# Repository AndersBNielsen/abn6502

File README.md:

# ABNielsen.com 6502 Single Board Computer Revision 2

## Browser emulator

The self-contained [browser emulator](emulator/README.md) runs the real ABN6502 r2 ROM. [Try it online](https://www.imania.dk/abn6502-emulator/). From `emulator/`, run `npm test` and `npm run build`. Emulator code and bundled hardware/firmware assets have separate licenses; see [emulator/LICENSE.md](emulator/LICENSE.md).

This is a 6502-based complete single board computer intended to help during the global IC shortage. Why use new chips when you can reuse scrap?

## Update Update! The newest ABN6502 SBC R2 board is available as:
- Blank PCBs 
- Fully mounted PCBs including sockets and headers
- Kits with SMD components presoldered, limiting soldering to though hole components/sockets. 

All gold plated (ENIG) PCBs: https://www.imania.dk/index.php?currency=EUR&cPath=204&sort=5a&language=en

Coming soon: R2 video. 

Complete hardware overview of R1:

Video about the wireless bootloader:

Check out the NEW project on HackADay if you want to read more and see some pretty pictures :)

https://hackaday.io/project/184725-abn6502-sbc-r1

For R1 I got rid of the Padauk MCU without increasing the chip count!

# Build instructions:

1) Send gerber files from /hardware to your favorite board house (see "Getting a PCB" below) (or get a board from [my store](https://www.imania.dk/index.php?currency=EUR&cPath=204&sort=5a&language=en)) 
2) Build the firmware using assemble.sh (macOS/Linux) - this will also try to burn the main ROM using Minipro. Dependencies: [CC65] (https://github.com/cc65/cc65) and a way to burn the ROM's.
3) Source the IC's - the spirit of this project is to contribute as little as possible to the global IC shortage and get used chips locally or from Ebay/AliExpress/etc.
4) Burn the ROMs. I use a TL866II Plus variant for the actual ROMs.
5) Solder away. If you can solder 0805 components(poorly), you should be fine. Some optional components (the microUSB connector, the 3v3 regulator, and the RF-module) require a bit more skill.  
6) For the PS/2-keyboard I use the 6522's Shift Register, PB6, and a 74xx74 flip flop.  See my R1 Hardware overview at 7:46: https://youtu.be/w5cA64xof2I?t=466 This is now included on the board - instead of a PS/2 connector which can be harder to source I went with a USB-A-connector. Keyboard plugs straight into the board. 
7) Enjoy!

Optional:
Setup SSH keys with a Raspberry Pi, connect an nRF24L01+ compatible module to it and compile the wireless bootloader code in /software_linux

Also optional:
Microsoft BASIC can be enabled by cloning the msbasic Github repo into the same folder you cloned this repo.

> git clone https://github.com/mist64/msbasic.git

Then uncomment ;BASIC := 1 (Remove the ";") and run assemble.sh - this will let you run BASIC by pressing F4.
To change settings for BASIC, values can be changed in defines_abn6502.s

Also, please note that the current code assumes VRAM starts at $0800 rather than the default $2000 in the schematic - resistors will have pads for configuring in the next build, but for now it requires jumpers.

License: Attribution-NonCommercial 4.0 International (CC BY-NC 4.0) https://creativecommons.org/licenses/by-nc/4.0/

## Getting a PCB
This project is kindly sponsored by JLCPCB. They offer cheap, professional looking PCBs and super fast delivery.

Step 1: Get the gerber file zip package from the /hardware/jlc folder
[hardware/jlcpcb/production_files/GERBER-6502.zip](hardware/jlcpcb/production_files/GERBER-6502.zip) for instance.

Step 2: Upload to JLCPCB [https://jlcpcb.com/?from=Anders_N](https://jlcpcb.com/?from=Anders_N)

Step 3: Pick your color, surface finish and order.

You can use these affiliate links to get a board for $2 and also get $54 worth of New User Coupons at: https://jlcpcb.com/?from=Anders_N

And in case you also want to order a 3D-printed case you can use this link. 
How to Get a $7 3D Printing Coupon: [https://3d.jlcpcb.com/?from=Anders3DP](https://jlc3dp.com/?from=Anders_N)

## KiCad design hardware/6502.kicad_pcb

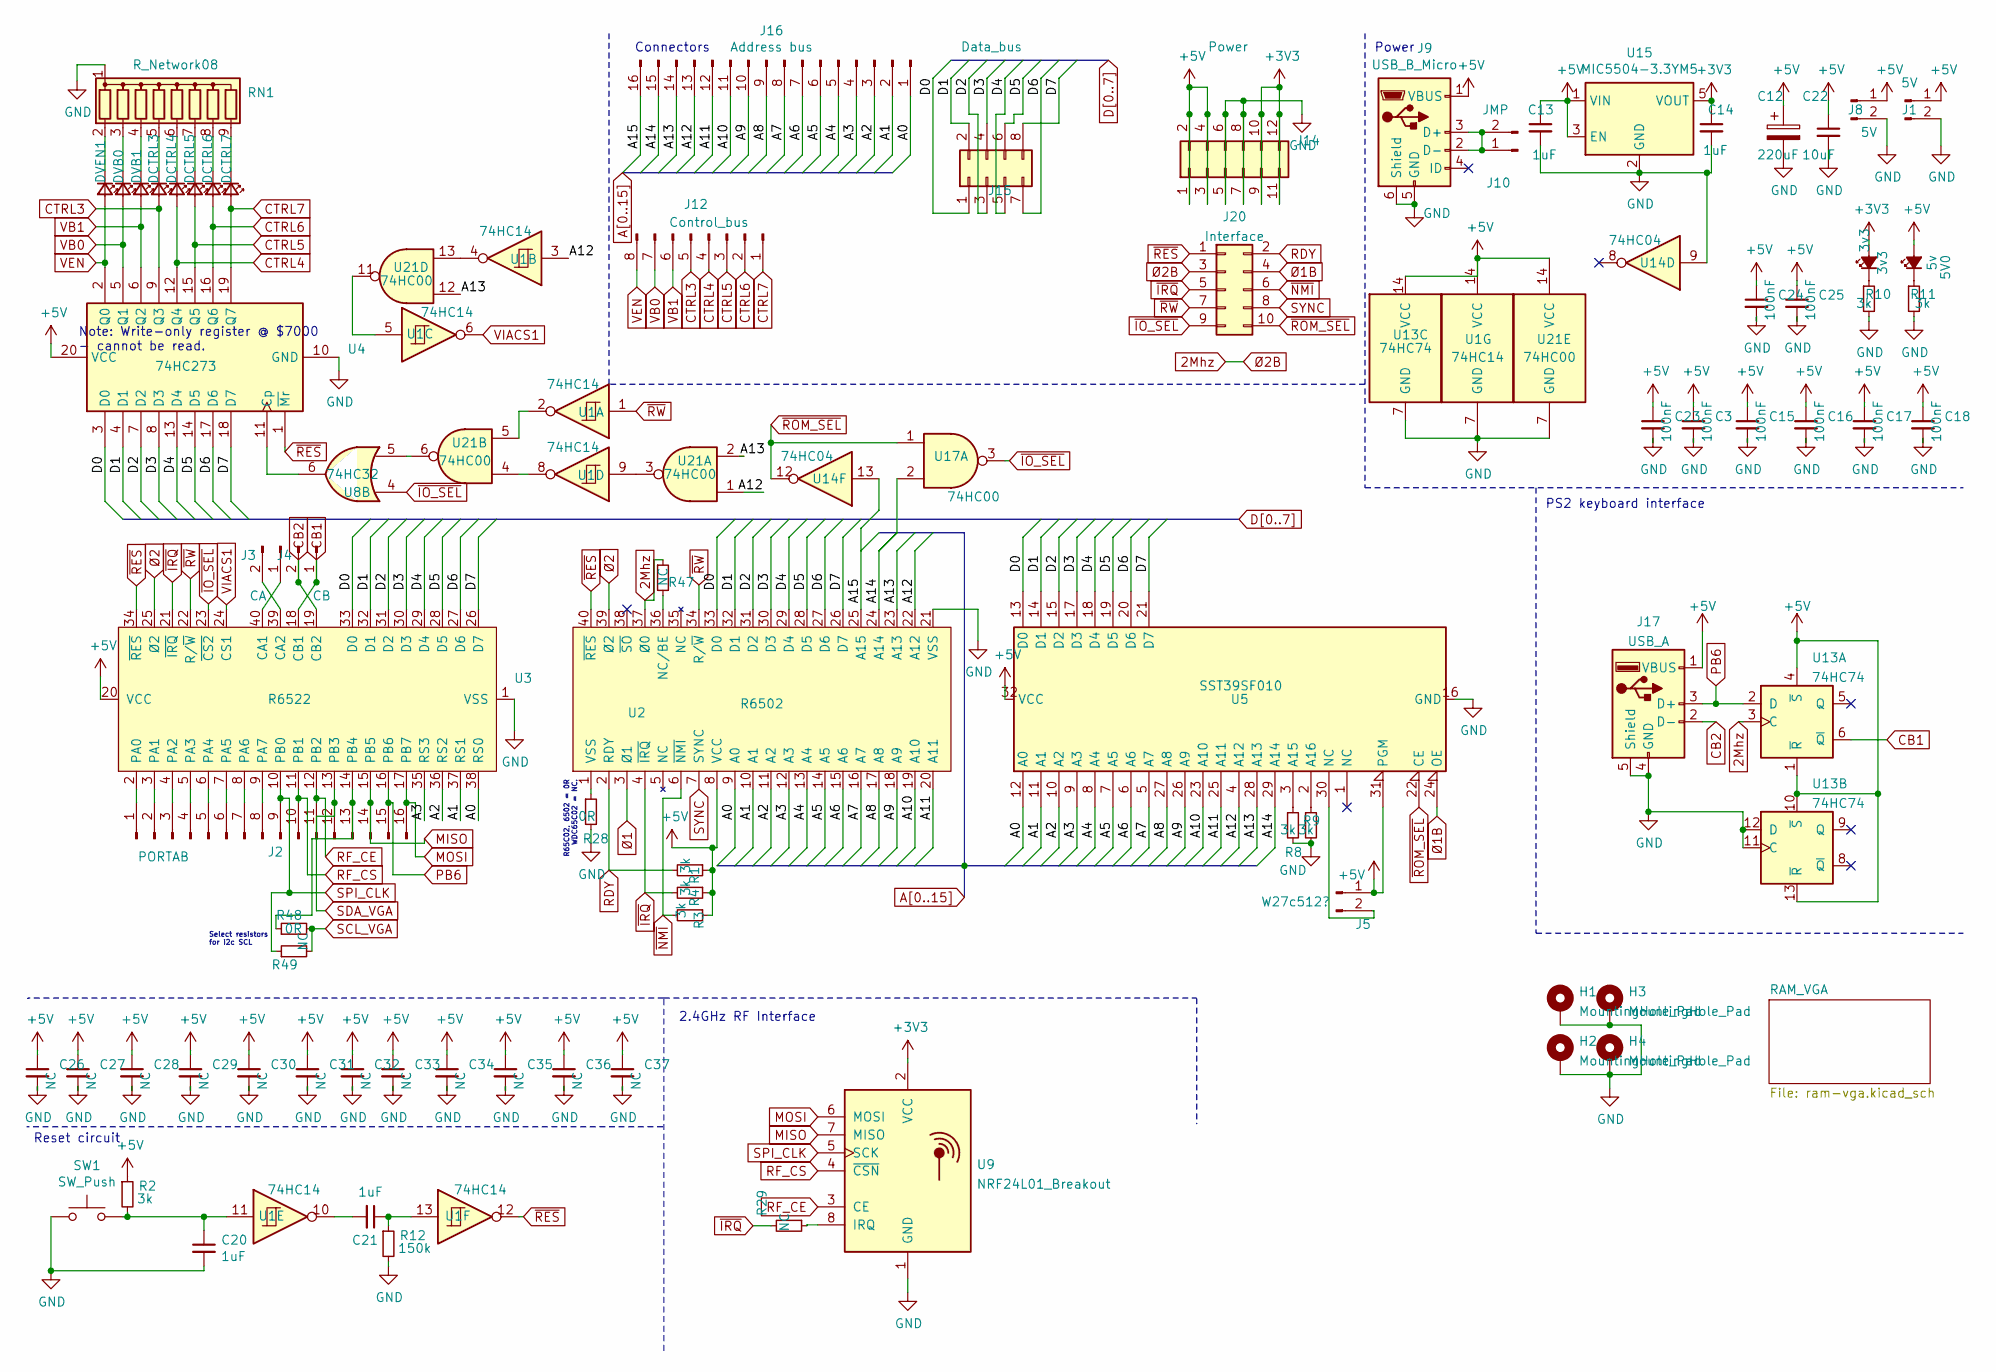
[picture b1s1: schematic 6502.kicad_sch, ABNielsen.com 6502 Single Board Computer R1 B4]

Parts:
3v3: 3v3; LED_0805_2012Metric; LCSC C84256
5V0: 5v; LED_0805_2012Metric; LCSC C84256
C3, C15, C16, C17, C18, C23, C24, C25: 100nF; C_0603_1608Metric
C12: 220uF; CP_Elec_6.3x7.7; LCSC C131120
C13, C14, C20, C21: 1uF; C_0805_2012Metric
C22: 10uF; C_0805_2012Metric
C26, C27, C28, C29, C30, C31, C32, C33, C34, C35, C36, C37: NC; C_0805_2012Metric
DCTRL3, DCTRL4, DCTRL5, DCTRL6, DCTRL7: RED; LED_0805_2012Metric; LCSC C84256
DVB0, DVB1: RED; LED_0805_2012Metric; LCSC C84256
DVEN1: RED; LED_0805_2012Metric; LCSC C84256
H1, H2, H3, H4: MountingHole_Pad; MountingHole_4.3mm_M4_ISO14580_Pad
J1, J8: 5V; PinHeader_1x02_P2.54mm_Vertical
J2: PORTAB; PinHeader_1x16_P2.54mm_Vertical
J3: CA; PinHeader_1x02_P2.54mm_Vertical
J4: CB; PinHeader_1x02_P2.54mm_Vertical
J5: W27c512?; PinHeader_1x02_P2.54mm_Vertical
J9: USB_B_Micro; USB_Micro-B_Amphenol_10118194_Horizontal; LCSC C132563
J10: JMP; PinHeader_1x02_P2.54mm_Vertical
J12: Control_bus; PinHeader_1x08_P2.54mm_Vertical
J14: Power; PinHeader_2x06_P2.54mm_Vertical
J15: Data_bus; PinHeader_2x04_P2.54mm_Vertical
J16: Address bus; PinHeader_2x08_P2.54mm_Vertical
J17: USB_A; USB_A_Molex_67643_Horizontal
J20: Interface; PinHeader_2x05_P2.54mm_Vertical
R1, R2, R3, R4, R8, R9, R10, R11: 3k; R_0805_2012Metric
R12: 150k; R_0805_2012Metric
R28: 0R; SolderJumper-2_P1.3mm_Open_RoundedPad1.0x1.5mm
R29, R47: NC; SolderJumper-2_P1.3mm_Open_RoundedPad1.0x1.5mm
R48: 0R; R_0805_2012Metric
R49: NC; R_0805_2012Metric
RN1: R_Network08; R_Array_SIP9
SW1: SW_Push; SW_SPST_TL3342; LCSC C318884
U1: 74HC14; DIP-14_W7.62mm
U2: R6502; DIP-40_W15.24mm
U3: R6522; DIP-40_W15.24mm
U4: 74HC273; DIP-20_W7.62mm
U5: SST39SF010; DIP_Socket-32_W11.9_W12.7_W15.24_W17.78_W18.5_3M_232-1285-0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
U8: 74HC32; DIP-14_W7.62mm
U9: NRF24L01_Breakout; NRF24L01-SMD
U13: 74HC74; DIP-14_W7.62mm
U14: 74HC04; DIP-14_W7.62mm
U15: MIC5504-3.3YM5; SOT-23-5; LCSC C3021093
U17, U21: 74HC00; DIP-14_W7.62mm

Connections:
2Mhz: J20.3, R47.1, U2.37 (Ø0), U13.3 (C); also elsewhere on the board
+3V3: 3v3.2 (A), C14.1, J14.9, J14.10, J14.11, J14.12, U9.2 (VCC), U15.5 (VOUT)
+5V: 5V0.2 (A), C3.1, C12.1, C13.1, C15.1, C16.1, C17.1, C18.1, C22.1, C23.1, C24.1, C25.1, C26.1, C27.1, C28.1, C29.1, C30.1, C31.1, C32.1, C33.1, C34.1, C35.1, C36.1, C37.1, J1.1, J5.1, J8.1, J9.1 (VBUS), J9.A4 (VBUS), J9.A9 (VBUS), J9.B4 (VBUS), J9.B9 (VBUS), J14.1, J14.2, J14.3, J14.4, J17.1 (VBUS), R1.1, R2.1, R3.1, R4.1, U1.14 (VCC), U2.8 (VCC), U3.20 (VCC), U4.20 (VCC), U5.31 (PGM), U5.32 (VCC), U13.1 (~R), U13.4 (~S), U13.10 (~S), U13.13 (~R), U13.14 (VCC), U15.1 (VIN), U15.3 (EN), U21.14 (VCC); also elsewhere on the board
A0: J16.1, U2.9 (A0), U3.38 (RS0), U5.12 (A0); also elsewhere on the board
A1: J16.2, U2.10 (A1), U3.37 (RS1), U5.11 (A1); also elsewhere on the board
A2: J16.3, U2.11 (A2), U3.36 (RS2), U5.10 (A2); also elsewhere on the board
A3: J16.4, U2.12 (A3), U3.35 (RS3), U5.9 (A3); also elsewhere on the board
A4: J16.5, U2.13 (A4), U5.8 (A4); also elsewhere on the board
A5: J16.6, U2.14 (A5), U5.7 (A5); also elsewhere on the board
A6: J16.7, U2.15 (A6), U5.6 (A6); also elsewhere on the board
A7: J16.8, U2.16 (A7), U5.5 (A7); also elsewhere on the board
A8: J16.9, U2.17 (A8), U5.27 (A8); also elsewhere on the board
A9: J16.10, U2.18 (A9), U5.26 (A9); also elsewhere on the board
A10: J16.11, U2.19 (A10), U5.23 (A10); also elsewhere on the board
A11: J16.12, U2.20 (A11), U5.25 (A11); also elsewhere on the board
A12: J16.13, U1.3, U2.22 (A12), U5.4 (A12), U21.1; also elsewhere on the board
A13: J16.14, U2.23 (A13), U5.28 (A13), U21.2, U21.12; also elsewhere on the board
A14: J16.15, U2.24 (A14), U5.29 (A14), U17.2; also elsewhere on the board
A15: J16.16, U2.25 (A15), U14.13; also elsewhere on the board
CB1: J4.1, U3.18 (CB1), U13.6 (~Q)
CB2: J4.2, J17.2 (D-), U3.19 (CB2)
CTRL3: DCTRL3.2 (A), J12.5, U4.9 (Q3); also elsewhere on the board
CTRL4: DCTRL4.2 (A), J12.4, U4.12 (Q4); also elsewhere on the board
CTRL5: DCTRL5.2 (A), J12.3, U4.15 (Q5); also elsewhere on the board
CTRL6: DCTRL6.2 (A), J12.2, U4.16 (Q6); also elsewhere on the board
CTRL7: DCTRL7.2 (A), J12.1, U4.19 (Q7)
D0: J15.1, U2.33 (D0), U3.33 (D0), U4.3 (D0), U5.13 (D0); also elsewhere on the board
D1: J15.2, U2.32 (D1), U3.32 (D1), U4.4 (D1), U5.14 (D1); also elsewhere on the board
D2: J15.3, U2.31 (D2), U3.31 (D2), U4.7 (D2), U5.15 (D2); also elsewhere on the board
D3: J15.4, U2.30 (D3), U3.30 (D3), U4.8 (D3), U5.17 (D3); also elsewhere on the board
D4: J15.5, U2.29 (D4), U3.29 (D4), U4.13 (D4), U5.18 (D4); also elsewhere on the board
D5: J15.6, U2.28 (D5), U3.28 (D5), U4.14 (D5), U5.19 (D5); also elsewhere on the board
D6: J15.7, U2.27 (D6), U3.27 (D6), U4.17 (D6), U5.20 (D6); also elsewhere on the board
D7: J15.8, U2.26 (D7), U3.26 (D7), U4.18 (D7), U5.21 (D7); also elsewhere on the board
MISO: J2.14, U3.15 (PB5), U9.7 (MISO)
MOSI: J2.16, U3.17 (PB7), U9.6 (MOSI)
unnamed: 3v3.1 (K), R10.1
unnamed: 5V0.1 (K), R11.1
unnamed: C20.1, R2.2, SW1.2, U1.11
unnamed: C21.1, R12.1, U1.13
unnamed: C21.2, U1.10
unnamed 65: DCTRL3.1 (K), RN1.5 (R4); also elsewhere on the board
unnamed 66: DCTRL4.1 (K), RN1.6 (R5); also elsewhere on the board
unnamed 67: DCTRL5.1 (K), RN1.7 (R6); also elsewhere on the board
unnamed 68: DCTRL6.1 (K), RN1.8 (R7); also elsewhere on the board
unnamed 69: DCTRL7.1 (K), RN1.9 (R8); also elsewhere on the board
unnamed 70: DVB0.1 (K), RN1.3 (R2); also elsewhere on the board
unnamed 71: DVB1.1 (K), RN1.4 (R3); also elsewhere on the board
unnamed 72: DVEN1.1 (K), RN1.2 (R1); also elsewhere on the board
unnamed: J2.1, U3.2 (PA0)
unnamed: J2.2, U3.3 (PA1)
unnamed: J2.3, U3.4 (PA2)
unnamed: J2.4, U3.5 (PA3)
unnamed: J2.5, U3.6 (PA4)
unnamed: J2.6, U3.7 (PA5)
unnamed: J2.7, U3.8 (PA6)
unnamed: J2.8, U3.9 (PA7)
unnamed: J3.1, U3.40 (CA1)
unnamed: J3.2, U3.39 (CA2)
unnamed: J5.2, U5.30 (NC)
unnamed 85: J9.A5 (CC1); also elsewhere on the board
unnamed 86: J9.B5 (CC2); also elsewhere on the board
unnamed: U1.2, U21.5
unnamed: U1.4, U21.13
unnamed: U1.5, U21.11
unnamed: U1.8, U21.4
unnamed: U1.9, U21.3
unnamed: R47.2, U2.36 (NC/BE)
unnamed: U4.11 (Cp), U8.6
unnamed: R8.1, U5.3 (A15)
unnamed: R9.1, U5.2 (A16)
unnamed: R29.1, U9.8 (IRQ)
unnamed: U8.5, U21.6
PB6: J2.15, J17.3 (D+), U3.16 (PB6), U13.2 (D)
RDY: J20.2, R1.2, U2.2 (RDY)
RF_CE: J2.11, U3.12 (PB2), U9.3 (CE)
RF_CS: J2.10, U3.11 (PB1), U9.4 (~CSN)
SDA_VGA: J2.12, U3.13 (PB3); also elsewhere on the board
SPI_CLK: J2.9, R49.1, U3.10 (PB0), U9.5 (SCK)
SYNC: J20.8, U2.7 (SYNC)
VB0: DVB0.2 (A), J12.7, U4.5 (Q1); also elsewhere on the board
VB1: DVB1.2 (A), J12.6, U4.6 (Q2); also elsewhere on the board
VEN: DVEN1.2 (A), J12.8, U4.2 (Q0); also elsewhere on the board
VIACS1: U1.6, U3.24 (CS1)
~IO_SEL: J20.9, U3.23 (~CS2), U8.4, U17.3
~IRQ: J20.5, R4.2, R29.2, U2.4 (~IRQ), U3.21 (~IRQ)
~NMI: J20.6, R3.2, U2.6 (~NMI)
~RES: J20.1, U1.12, U2.40 (~RES), U3.34 (~RES), U4.1 (~Mr)
~ROM_SEL: J20.10, U5.22 (CE), U14.12, U17.1
~RW: J20.7, U1.1, U2.34 (R/~W), U3.22 (R/~W); also elsewhere on the board
Ø1: U2.3 (Ø1)
Ø1B: J20.4, U5.24 (OE); also elsewhere on the board
Ø2: U2.39 (Ø2), U3.25 (Ø2)

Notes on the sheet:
Note: Write-only register @ $7000 - cannot be read.
Select resistors for i2c SCL
Power
R65C02, 6502 = 0R WDC65C02 = NC.
Reset circuit
Connectors
PS2 keyboard interface
2.4GHz RF Interface

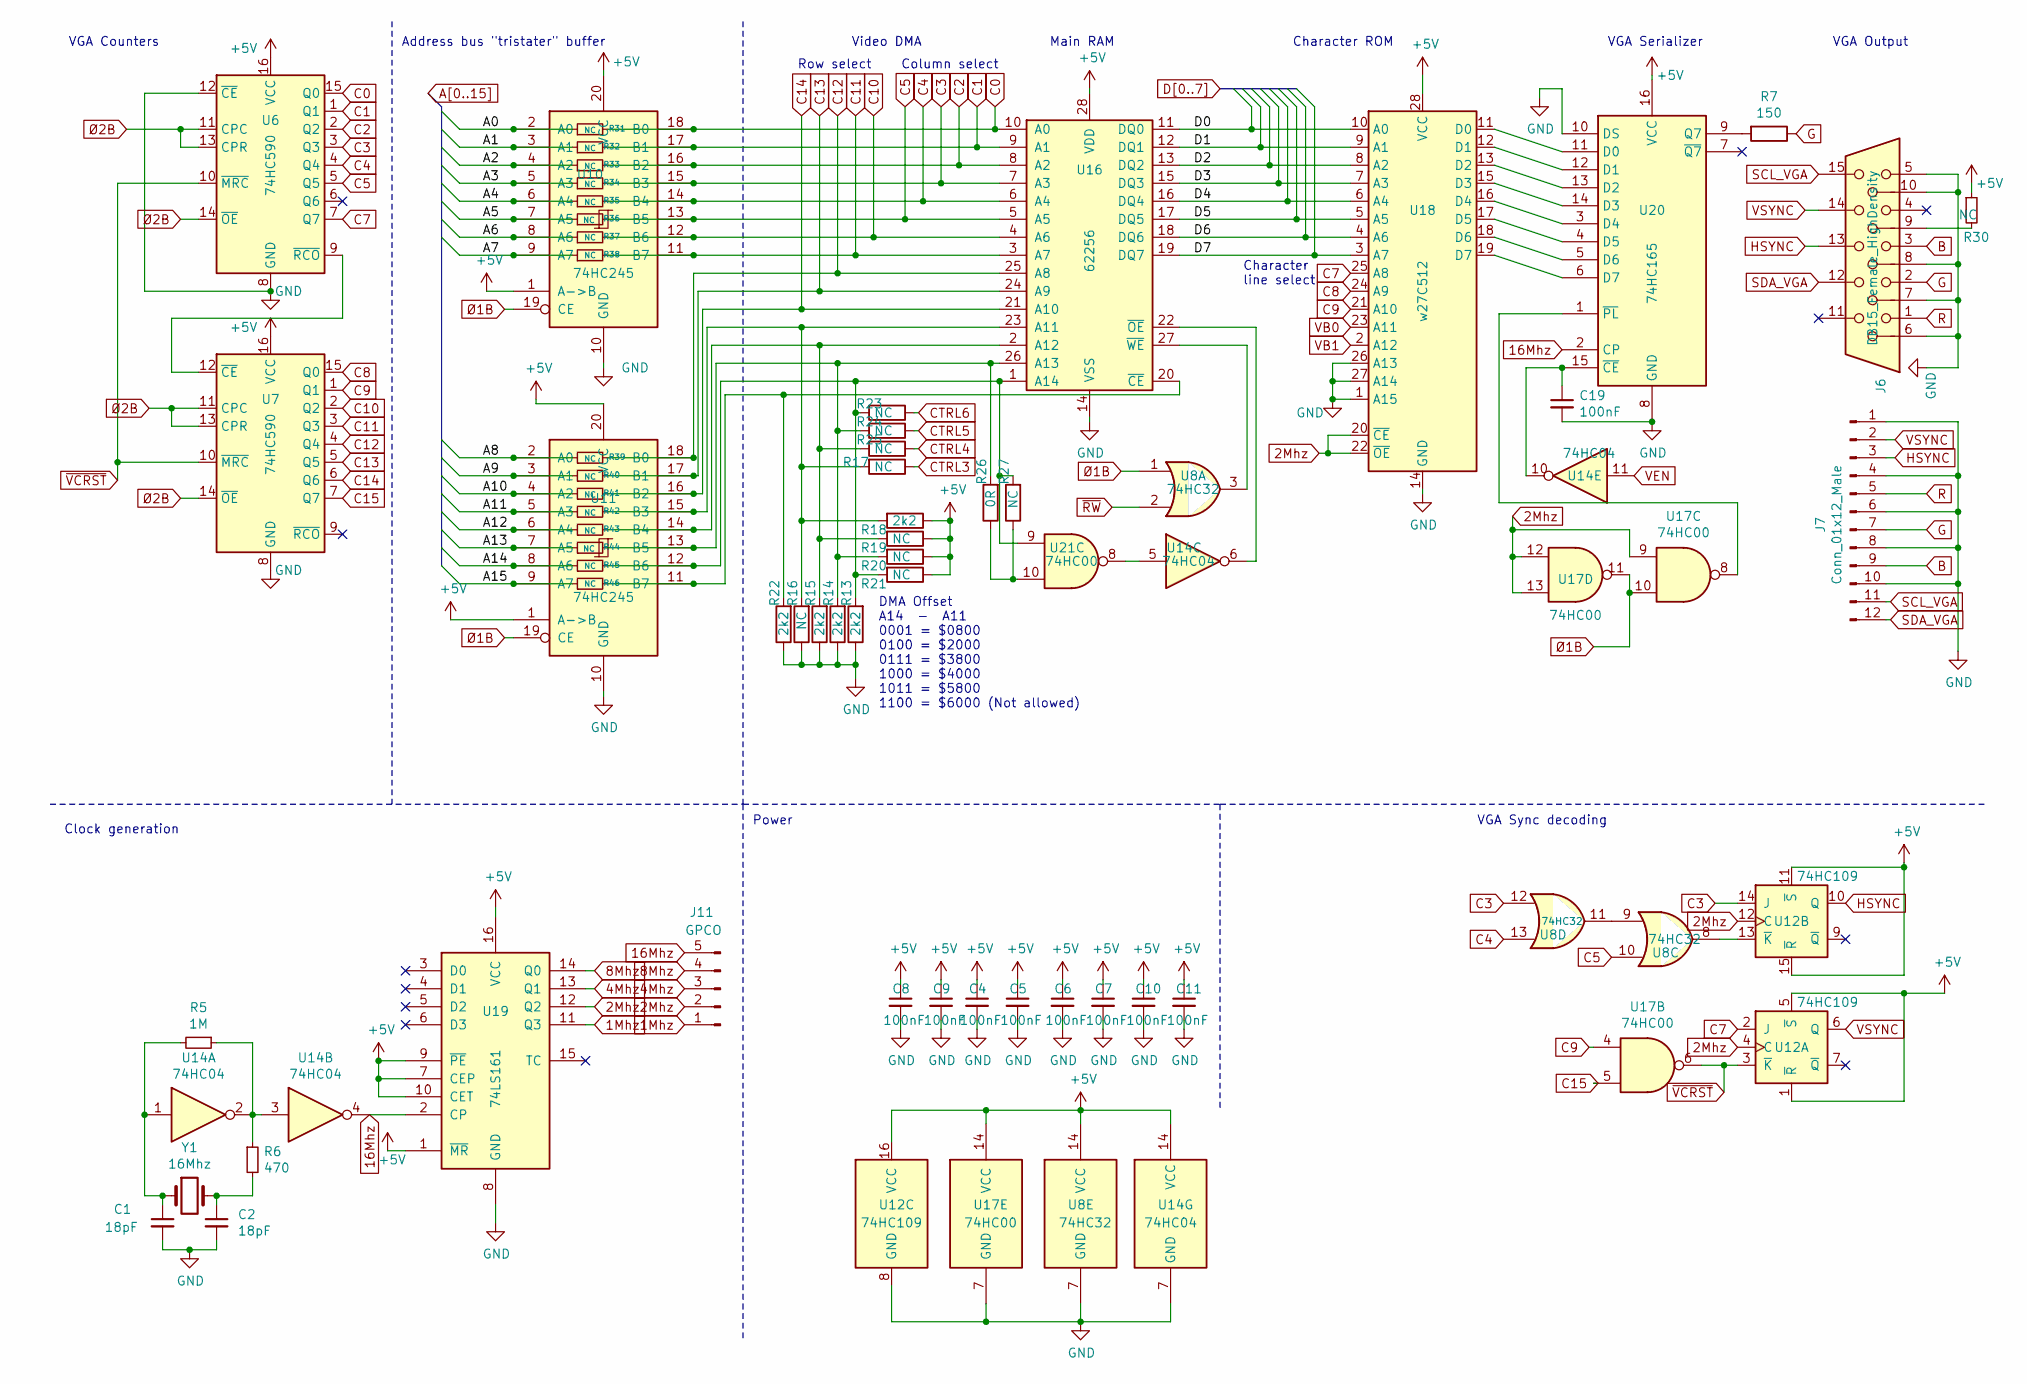
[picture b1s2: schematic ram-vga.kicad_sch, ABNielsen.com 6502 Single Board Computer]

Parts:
C1, C2: 18pF; C_0805_2012Metric
C4, C5, C6, C7, C8, C9, C10, C11, C19: 100nF; C_0603_1608Metric
J6: DB15_Female_HighDensity; DSUB-15-HD_Female_Horizontal_P2.29x2.54mm_EdgePinOffset9.40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
J7: Conn_01x12_Male; PinHeader_1x12_P2.54mm_Vertical
J11: GPCO; PinHeader_1x05_P2.54mm_Vertical
R5: 1M; R_0805_2012Metric
R6: 470; R_0805_2012Metric
R7: 150; R_0805_2012Metric
R13, R14, R15, R18, R22: 2k2; R_0805_2012Metric
R16, R17, R19, R20, R21, R23, R24, R25: NC; R_0805_2012Metric
R26: 0R; SolderJumper-2_P1.3mm_Open_RoundedPad1.0x1.5mm
R27, R30, R31, R32, R33, R34, R35, R36, R37, R38, R39, R40, R41, R42, R43, R44, R45, R46: NC; SolderJumper-2_P1.3mm_Open_RoundedPad1.0x1.5mm
U6, U7: 74HC590; DIP-16_W7.62mm
U8: 74HC32; DIP-14_W7.62mm
U10, U11: 74HC245; DIP-20_W7.62mm
U12: 74HC109; DIP-16_W7.62mm
U14: 74HC04; DIP-14_W7.62mm
U16: 62256; DIP-28_W15.24mm
U17, U21: 74HC00; DIP-14_W7.62mm
U18: w27C512; DIP-28_W15.24mm
U19: 74LS161; DIP-16_W7.62mm
U20: 74HC165; DIP-16_W7.62mm
Y1: 16Mhz; Crystal_HC49-U_Vertical

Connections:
1Mhz: J11.1, U19.11 (Q3)
2Mhz: J11.2, U6.11 (CPC), U6.13 (CPR), U6.14 (~OE), U7.11 (CPC), U7.13 (CPR), U7.14 (~OE), U12.4 (C), U12.12 (C), U17.9, U17.12, U17.13, U18.20 (~CE), U18.22 (~OE), U19.12 (Q2); also elsewhere on the board
4Mhz: J11.3, U19.13 (Q1)
8Mhz: J11.4, U19.14 (Q0)
16Mhz: J11.5, U14.4, U19.2 (CP), U20.2 (CP)
+5V: C4.1, C5.1, C6.1, C7.1, C8.1, C9.1, C10.1, C11.1, R18.1, R19.1, R20.1, R21.1, R30.1, U6.16 (VCC), U7.16 (VCC), U8.14 (VCC), U10.1 (A->B), U10.20 (VCC), U11.1 (A->B), U11.20 (VCC), U12.1 (~R), U12.5 (~S), U12.11 (~S), U12.15 (~R), U12.16 (VCC), U14.14 (VCC), U16.28 (VDD), U17.14 (VCC), U18.28 (VCC), U19.1 (~MR), U19.7 (CEP), U19.9 (~PE), U19.10 (CET), U19.16 (VCC), U20.16 (VCC); also elsewhere on the board
A0: R31.1, U10.2 (A0); also elsewhere on the board
A1: R32.1, U10.3 (A1); also elsewhere on the board
A2: R33.1, U10.4 (A2); also elsewhere on the board
A3: R34.1, U10.5 (A3); also elsewhere on the board
A4: R35.1, U10.6 (A4); also elsewhere on the board
A5: R36.1, U10.7 (A5); also elsewhere on the board
A6: R37.1, U10.8 (A6); also elsewhere on the board
A7: R38.1, U10.9 (A7); also elsewhere on the board
A8: R39.1, U11.2 (A0); also elsewhere on the board
A9: R40.1, U11.3 (A1); also elsewhere on the board
A10: R41.1, U11.4 (A2); also elsewhere on the board
A11: R42.1, U11.5 (A3); also elsewhere on the board
A12: R43.1, U11.6 (A4); also elsewhere on the board
A13: R44.1, U11.7 (A5); also elsewhere on the board
A14: R45.1, U11.8 (A6); also elsewhere on the board
A15: R46.1, U11.9 (A7); also elsewhere on the board
B: J6.3, J7.9
C0: R31.2, U6.15 (Q0), U10.18 (B0), U16.10 (A0)
C1: R32.2, U6.1 (Q1), U10.17 (B1), U16.9 (A1)
C2: R33.2, U6.2 (Q2), U10.16 (B2), U16.8 (A2)
C3: R34.2, U6.3 (Q3), U8.12, U10.15 (B3), U12.14 (J), U16.7 (A3)
C4: R35.2, U6.4 (Q4), U8.13, U10.14 (B4), U16.6 (A4)
C5: R36.2, U6.5 (Q5), U8.10, U10.13 (B5), U16.5 (A5)
C7: U6.7 (Q7), U12.2 (J), U18.25 (A8)
C8: U7.15 (Q0), U18.24 (A9)
C9: U7.1 (Q1), U17.4, U18.21 (A10)
C10: R37.2, U7.2 (Q2), U10.12 (B6), U16.4 (A6)
C11: R38.2, U7.3 (Q3), U10.11 (B7), U16.3 (A7)
C12: R39.2, U7.4 (Q4), U11.18 (B0), U16.25 (A8)
C13: R40.2, U7.5 (Q5), U11.17 (B1), U16.24 (A9)
C14: R41.2, U7.6 (Q6), U11.16 (B2), U16.21 (A10)
C15: U7.7 (Q7), U17.5
CTRL3: R17.1; also elsewhere on the board
CTRL4: R25.1; also elsewhere on the board
CTRL5: R24.1; also elsewhere on the board
CTRL6: R23.1; also elsewhere on the board
D0: U16.11 (DQ0), U18.10 (A0); also elsewhere on the board
D1: U16.12 (DQ1), U18.9 (A1); also elsewhere on the board
D2: U16.13 (DQ2), U18.8 (A2); also elsewhere on the board
D3: U16.15 (DQ3), U18.7 (A3); also elsewhere on the board
D4: U16.16 (DQ4), U18.6 (A4); also elsewhere on the board
D5: U16.17 (DQ5), U18.5 (A5); also elsewhere on the board
D6: U16.18 (DQ6), U18.4 (A6); also elsewhere on the board
D7: U16.19 (DQ7), U18.3 (A7); also elsewhere on the board
G: J6.2, J7.7, R7.1
HSYNC: J6.13, J7.3, U12.10 (Q)
unnamed 60: C1.1, R5.2, U14.1, Y1.1; also elsewhere on the board
unnamed 61: C2.1, R6.2, Y1.2; also elsewhere on the board
unnamed: J6.9, R30.2
unnamed: R5.1, R6.1, U14.2, U14.3
unnamed: R26.1 (A), R27.1 (A), U21.10
unnamed: R14.2, R20.2, R24.2, R26.2 (B), R44.2, U11.13 (B5), U16.26 (A13)
unnamed: R13.2, R21.2, R23.2, R27.2 (B), R45.2, U11.12 (B6), U16.1 (A14), U21.9
unnamed: U6.9 (~RCO), U7.12 (~CE)
unnamed: U8.9, U8.11
unnamed: R16.2, R17.2, R18.2, R42.2, U11.15 (B3), U16.23 (A11)
unnamed: R15.2, R19.2, R25.2, R43.2, U11.14 (B4), U16.2 (A12)
unnamed: R22.2, R46.2, U11.11 (B7), U16.20 (~CE)
unnamed: U8.8, U12.13 (~K)
unnamed: U14.5, U21.8
unnamed: U14.6, U16.22 (~OE)
unnamed: U8.3, U16.27 (~WE)
unnamed: U18.11 (D0), U20.11 (D0)
unnamed: U18.12 (D1), U20.12 (D1)
unnamed: U18.13 (D2), U20.13 (D2)
unnamed: U18.15 (D3), U20.14 (D3)
unnamed: U18.16 (D4), U20.3 (D4)
unnamed: U18.17 (D5), U20.4 (D5)
unnamed: U18.18 (D6), U20.5 (D6)
unnamed: U18.19 (D7), U20.6 (D7)
unnamed: R7.2, U20.9 (Q7)
unnamed: C19.1, U14.10, U20.15 (~CE)
unnamed: U17.8, U20.1 (~PL)
R: J6.1, J7.5
SDA_VGA: J6.12, J7.12; also elsewhere on the board
VB0: U18.23 (A11); also elsewhere on the board
VB1: U18.2 (A12); also elsewhere on the board
VEN: U14.11; also elsewhere on the board
VSYNC: J6.14, J7.2, U12.6 (Q)
~RW: U8.2; also elsewhere on the board
~VCRST: U6.10 (~MRC), U7.10 (~MRC), U12.3 (~K), U17.6
Ø1B: U8.1, U10.19 (CE), U11.19 (CE), U17.10, U17.11; also elsewhere on the board

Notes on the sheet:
Row select
VGA Counters
VGA Sync decoding
DMA Offset A14 - A11 0001 = $0800 0100 = $2000 0111 = $3800 1000 = $4000 1011 = $5800 1100 = $6000 (Not allowed)
Address bus "tristater" buffer
Character ROM
VGA Output
Video DMA
VGA Serializer
Character line select
Column select
Clock generation
Main RAM
Power

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
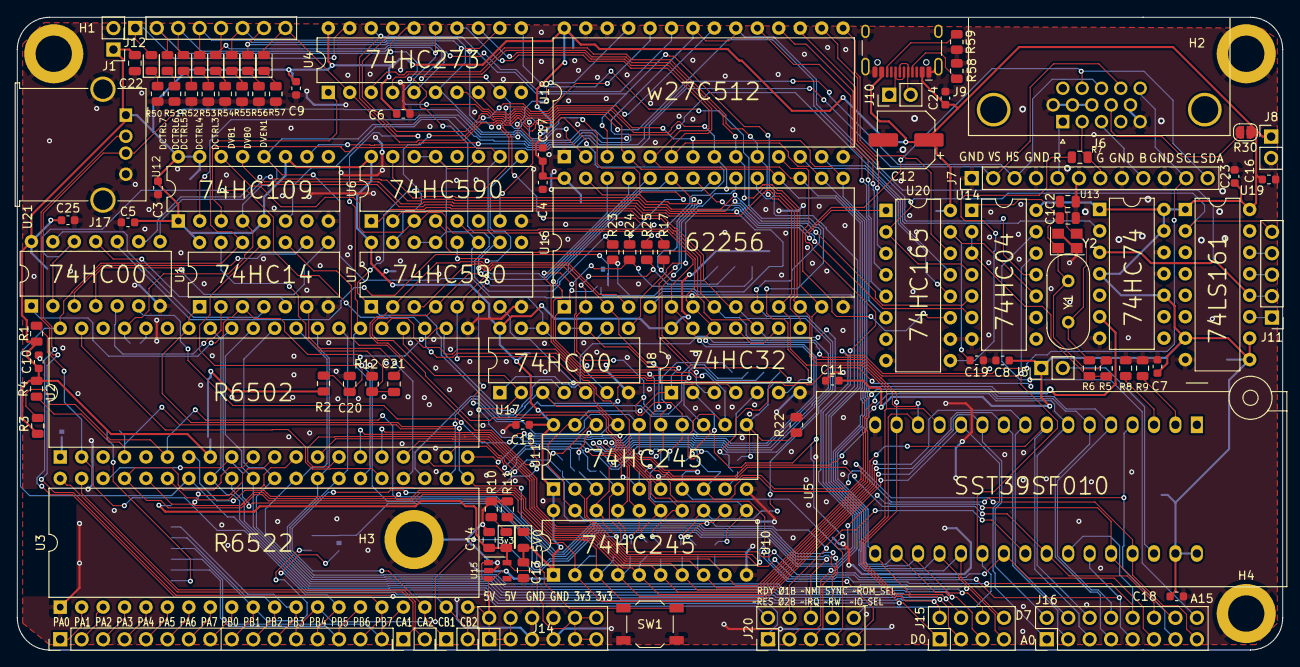
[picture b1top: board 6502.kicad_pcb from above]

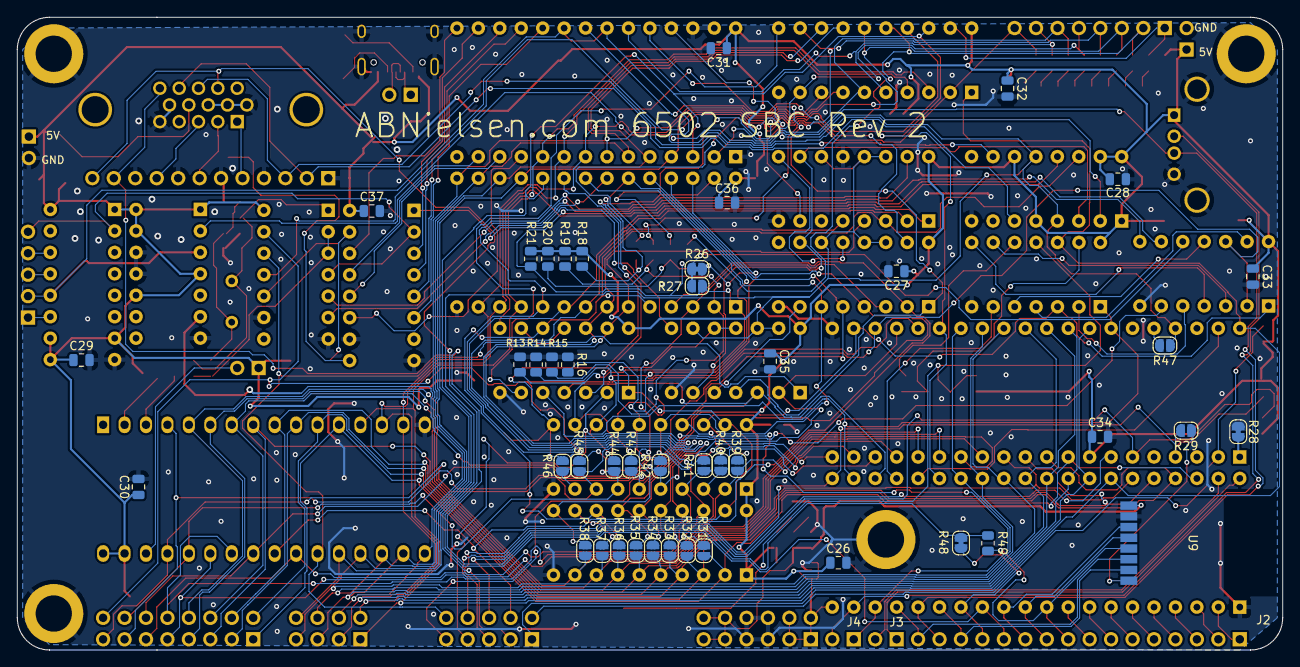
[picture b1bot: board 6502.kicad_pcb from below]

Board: 2 copper layers, 149.9 x 74.9 mm, 151 parts (44 on the bottom side), 150 nets.

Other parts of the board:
R50, R51, R52, R53, R54, R55, R56, R57: 3k; R_0805_2012Metric
R58, R59: 5k1; R_0805_2012Metric
Y2: 16Mhz; Crystal_SMD_3225-4Pin_3.2x2.5mm

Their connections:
unnamed 60: Y2.1; also elsewhere on the board
unnamed 61: Y2.3; also elsewhere on the board
unnamed 65: R54.2; also elsewhere on the board
unnamed 66: R53.2; also elsewhere on the board
unnamed 67: R52.2; also elsewhere on the board
unnamed 68: R51.2; also elsewhere on the board
unnamed 69: R50.2; also elsewhere on the board
unnamed 70: R56.2; also elsewhere on the board
unnamed 71: R55.2; also elsewhere on the board
unnamed 72: R57.2; also elsewhere on the board
unnamed 85: R58.1; also elsewhere on the board
unnamed 86: R59.1; also elsewhere on the board

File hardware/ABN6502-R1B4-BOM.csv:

Comment,Designator,Footprint,LCSC
"3v3","3v3","LED_SMD:LED_0805_2012Metric","C84256"
"5v","5V0","LED_SMD:LED_0805_2012Metric","C84256"
"18pF","C1,C2","Capacitor_SMD:C_0805_2012Metric",""
"220uF","C12","Capacitor_SMD:CP_Elec_6.3x7.7","C131120"
"1uF","C13,C14,C20,C21","Capacitor_SMD:C_0805_2012Metric",""
"10uF","C22","Capacitor_SMD:C_0805_2012Metric",""
"NC","C26,C27,C28,C29,C30,C31,C32,C33,C34,C35,C36,C37","Capacitor_SMD:C_0805_2012Metric",""
"100nF","C3,C4,C5,C6,C7,C8,C9,C10,C11,C15,C16,C17,C18,C19,C23,C24,C25","Capacitor_SMD:C_0603_1608Metric",""
"RED","DVB0,DVB1,DVEN1,DCTRL3,DCTRL4,DCTRL5,DCTRL6,DCTRL7","LED_SMD:LED_0805_2012Metric","C84256"
"MountingHole_Pad","H1,H2,H3,H4","MountingHole:MountingHole_4.3mm_M4_ISO14580_Pad",""
"5V","J1,J8","Connector_PinHeader_2.54mm:PinHeader_1x02_P2.54mm_Vertical",""
"JMP","J10","Connector_PinHeader_2.54mm:PinHeader_1x02_P2.54mm_Vertical",""
"GPCO","J11","Connector_PinHeader_2.54mm:PinHeader_1x05_P2.54mm_Vertical",""
"Control_bus","J12","Connector_PinHeader_2.54mm:PinHeader_1x08_P2.54mm_Vertical",""
"Power","J14","Connector_PinHeader_2.54mm:PinHeader_2x06_P2.54mm_Vertical",""
"Data_bus","J15","Connector_PinHeader_2.54mm:PinHeader_2x04_P2.54mm_Vertical",""
"Address bus","J16","Connector_PinHeader_2.54mm:PinHeader_2x08_P2.54mm_Vertical",""
"USB_A","J17","Connector_USB:USB_A_Molex_67643_Horizontal",""
"PORTAB","J2","Connector_PinHeader_2.54mm:PinHeader_1x16_P2.54mm_Vertical",""
"Interface","J20","Connector_PinHeader_2.54mm:PinHeader_2x05_P2.54mm_Vertical",""
"CA","J3","Connector_PinHeader_2.54mm:PinHeader_1x02_P2.54mm_Vertical",""
"CB","J4","Connector_PinHeader_2.54mm:PinHeader_1x02_P2.54mm_Vertical",""
"W27c512?","J5","Connector_PinHeader_2.54mm:PinHeader_1x02_P2.54mm_Vertical",""
"DB15_Female_HighDensity","J6","Connector_Dsub:DSUB-15-HD_Female_Horizontal_P2.29x2.54mm_EdgePinOffset9.40mm-Mountingholes",""
"Conn_01x12_Male","J7","Connector_PinHeader_2.54mm:PinHeader_1x12_P2.54mm_Vertical",""
"USB_B_Micro","J9","Connector_USB:USB_Micro-B_Amphenol_10118194_Horizontal","C132563"
"3k","R1,R2,R3,R4,R8,R9,R10,R11","Resistor_SMD:R_0805_2012Metric",""
"150k","R12","Resistor_SMD:R_0805_2012Metric",""
"2k2","R13,R14,R15,R18,R22","Resistor_SMD:R_0805_2012Metric",""
"0R","R26,R28","Jumper:SolderJumper-2_P1.3mm_Open_RoundedPad1.0x1.5mm",""
"NC","R27,R29,R30,R31,R32,R33,R34,R35,R36,R37,R38,R39,R40,R41,R42,R43,R44,R45,R46,R47","Jumper:SolderJumper-2_P1.3mm_Open_RoundedPad1.0x1.5mm",""
"0R","R48","Resistor_SMD:R_0805_2012Metric",""
"NC","R16,R17,R19,R20,R21,R23,R24,R25,R49","Resistor_SMD:R_0805_2012Metric",""
"1M","R5","Resistor_SMD:R_0805_2012Metric",""
"470","R6","Resistor_SMD:R_0805_2012Metric",""
"150","R7","Resistor_SMD:R_0805_2012Metric",""
"R_Network08","RN1","Resistor_THT:R_Array_SIP9",""
"SW_Push","SW1","Button_Switch_SMD:SW_SPST_TL3342","C318884"
"74HC14","U1","Package_DIP:DIP-14_W7.62mm",""
"74HC245","U10,U11","Package_DIP:DIP-20_W7.62mm",""
"74HC109","U12","Package_DIP:DIP-16_W7.62mm",""
"74HC74","U13","Package_DIP:DIP-14_W7.62mm",""
"74HC04","U14","Package_DIP:DIP-14_W7.62mm",""
"MIC5504-3.3YM5","U15","Package_TO_SOT_SMD:SOT-23-5","C3021093"
"62256","U16","Package_DIP:DIP-28_W15.24mm",""
"74HC00","U17,U21","Package_DIP:DIP-14_W7.62mm",""
"w27C512","U18","Package_DIP:DIP-28_W15.24mm",""
"74LS161","U19","Package_DIP:DIP-16_W7.62mm",""
"R6502","U2","Package_DIP:DIP-40_W15.24mm",""
"74HC165","U20","Package_DIP:DIP-16_W7.62mm",""
"R6522","U3","Package_DIP:DIP-40_W15.24mm",""
"74HC273","U4","Package_DIP:DIP-20_W7.62mm",""
"SST39SF010","U5","Socket:DIP_Socket-32_W11.9_W12.7_W15.24_W17.78_W18.5_3M_232-1285-00-0602J",""
"74HC590","U6,U7","Package_DIP:DIP-16_W7.62mm",""
"74HC32","U8","Package_DIP:DIP-14_W7.62mm",""
"NRF24L01_Breakout","U9","mysensors_radios:NRF24L01-SMD",""
"16Mhz","Y1","Crystal:Crystal_HC49-U_Vertical",""

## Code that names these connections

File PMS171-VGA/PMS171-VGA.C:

#include	"extern.h"


//				P#, VDD, PA0,  PA3, PA4, PA5, PA6, PA7, GND, MASK1, MASK2, SHIF#
.writer package	16,	  5, 11,	9,	 10,  8,	7,	6,	 12, 0x00, 0x00, 0

VSYNC	BIT PA.4;
//HSYNC	BIT PA.4;
//HBLANK  BIT	PA.6;
VBLANK  BIT PA.7;
A13		BIT PA.3

byte mode = 0;
word line = 0;
word count = 0;

void	FPPA0 (void)
{
//	.ADJUST_IC	SYSCLK=IHRC/2, IHRC=15734375Hz, Vdd=5.0V		//	SYSCLK=IHRC/2
	.ADJUST_IC	SYSCLK=IHRC/2, IHRC=16000KHz, Vdd=5.0V		//	SYSCLK=IHRC/2

	//	clkmd.En_Reset	=	0;			//	PA.5 as Reset pin

	CLKMD = 0x35;
	//	Insert Initial Code

	paph.5 = 1; //Does this work?

	$ VSYNC HIGH, OUT;
	$ VBLANK HIGH, OUT;
	$ A13 LOW, OUT;

	PBC = 0xFF;
	PB = 0;

	line = 0;
	$ INTEN PA0;

		INTEGS = 0b0;
	INTRQ = 0;
	ENGINT;


	while (1)
	{
    if (line.8 == 1){
		A13 = 1;
		} else
			{
					A13 = 0;
			}
	if (line == 490) {
	$ VSYNC LOW;
		}

	if (line == 492) {
	$ VSYNC HIGH;
	}


	if (line == 524) {
	line = 0;
		   }

} //While 1
} //FPPA0

void	Interrupt (void)
{
	pushaf; //We don't care about flags - only timing... Or maybe we do?

	if (Intrq.PA0)
	{
		line++;
		PB = line;
		Intrq.PA0	=	0;

	}

	popaf;
}

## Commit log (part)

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2021-10-21 build folder
2021-10-21 Correct license
2021-10-30 PCB Silkscreen annotations added
2021-10-30 New PCB PDF
2022-04-03 Wireless nRF24L01+ bootloader added! No more Padauk PMS171b!
2022-04-12 Removed build output and .DS_Store files
2022-04-12 Updated BOM.
2022-05-27 PS/2 via shift register upgrade!
2022-07-21 Tape interface upgrade - still missing housekeeping bits
2022-09-18 BASIC interpreter support, PS/2 serial code, scrolling support, cleanup.
2022-10-18 R1B2 gerbers, start+stop bits in modem driver
2022-11-06 Delete bom.txt
    Outdated - BOM can be found on the hackaday.io page and in the kicad files
2022-11-24 Solder jumpers instead of 0402 resistors, redundant 0805 decoupling caps
2025-02-27 Silkscreen indicators, updated BOM and gerbers and stuff
2025-07-06 Revision 2 published
